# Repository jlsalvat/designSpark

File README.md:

# designSpark V10 files
cartes et bibliothèques

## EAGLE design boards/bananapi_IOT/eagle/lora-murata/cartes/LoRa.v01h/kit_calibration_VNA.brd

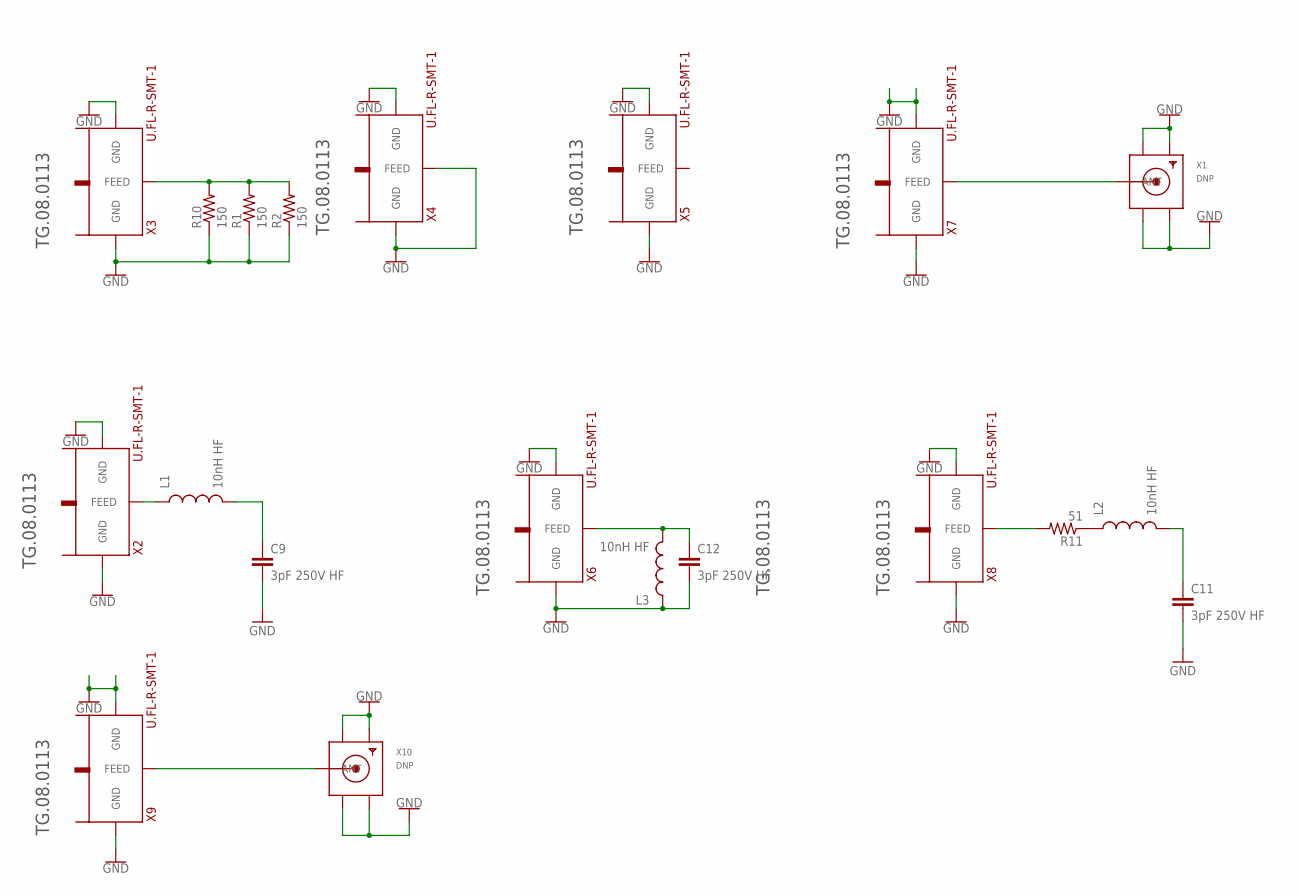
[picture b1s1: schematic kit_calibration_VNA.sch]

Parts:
C9, C11, C12: 3pF 250V HF; 0603-CAP
L1, L2, L3: 10nH HF; 0603
R1, R2, R10: 150; 0603-RES
R11: 51; 0603-RES
X1, X10: DNP; SMA_EDGELAUNCH; DIGIKEY CON-SMA-EDGE-S-ND
X2, X3, X4, X5, X6, X7, X8, X9: U.FL-R-SMT-1

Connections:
GND: C9.2, C11.2, C12.2, L3.1, R1.1, R2.1, R10.1, X1.GND@1 (GND4), X1.GND@2 (GND3), X1.GND@3 (GND2), X1.GND@4 (GND1), X2.P$1 (GND), X2.P$2 (GND), X3.P$1 (GND), X3.P$2 (GND), X4.P$1 (GND), X4.P$2 (GND), X4.P$3 (FEED), X5.P$1 (GND), X5.P$2 (GND), X6.P$1 (GND), X6.P$2 (GND), X7.P$1 (GND), X7.P$2 (GND), X8.P$1 (GND), X8.P$2 (GND), X9.P$1 (GND), X9.P$2 (GND), X10.GND@1 (GND4), X10.GND@2 (GND3), X10.GND@3 (GND2), X10.GND@4 (GND1)
unnamed: X9.P$3 (FEED), X10.P (ANT)
unnamed: C9.1, L1.2
unnamed: L2.1, R11.1
unnamed: R1.2, R2.2, R10.2, X3.P$3 (FEED)
unnamed: L1.1, X2.P$3 (FEED)
unnamed: R11.2, X8.P$3 (FEED)
unnamed: C11.1, L2.2
unnamed: C12.1, L3.2, X6.P$3 (FEED)
unnamed: X1.P (ANT), X7.P$3 (FEED)

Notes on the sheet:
TG.08.0113

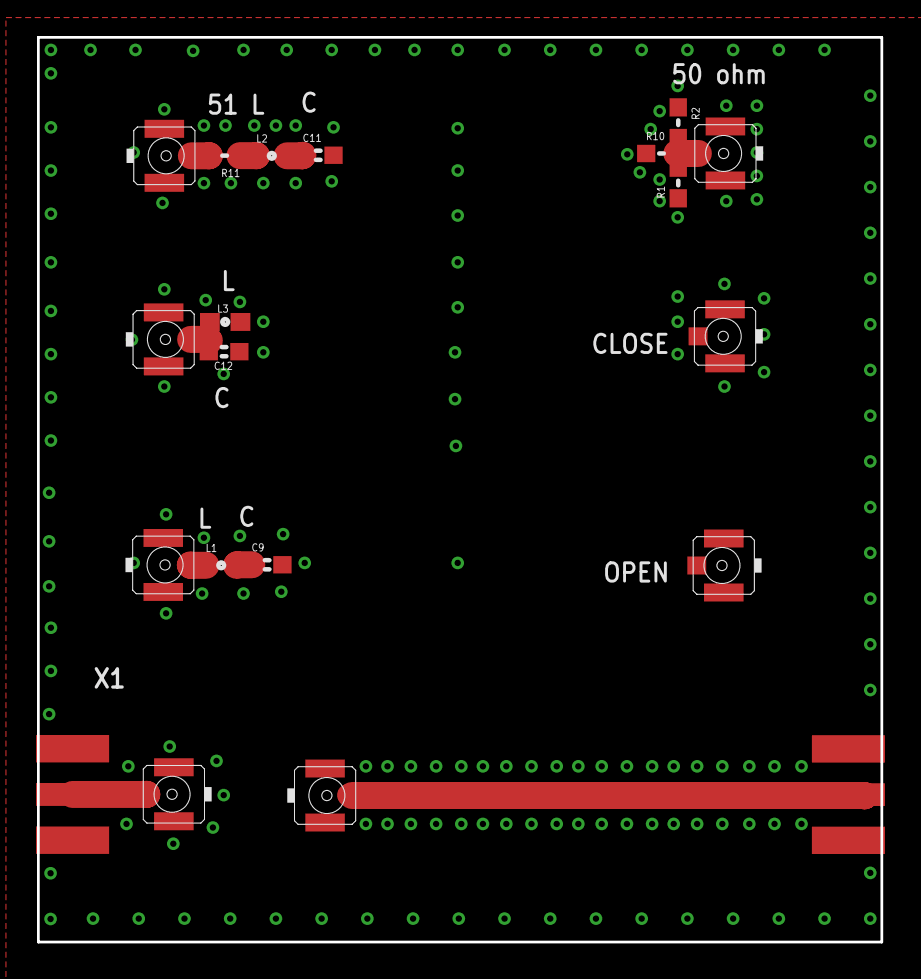
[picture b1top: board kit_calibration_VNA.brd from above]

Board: 2 copper layers, 46.9 x 50.3 mm, 20 parts (0 on the bottom side), 10 nets.

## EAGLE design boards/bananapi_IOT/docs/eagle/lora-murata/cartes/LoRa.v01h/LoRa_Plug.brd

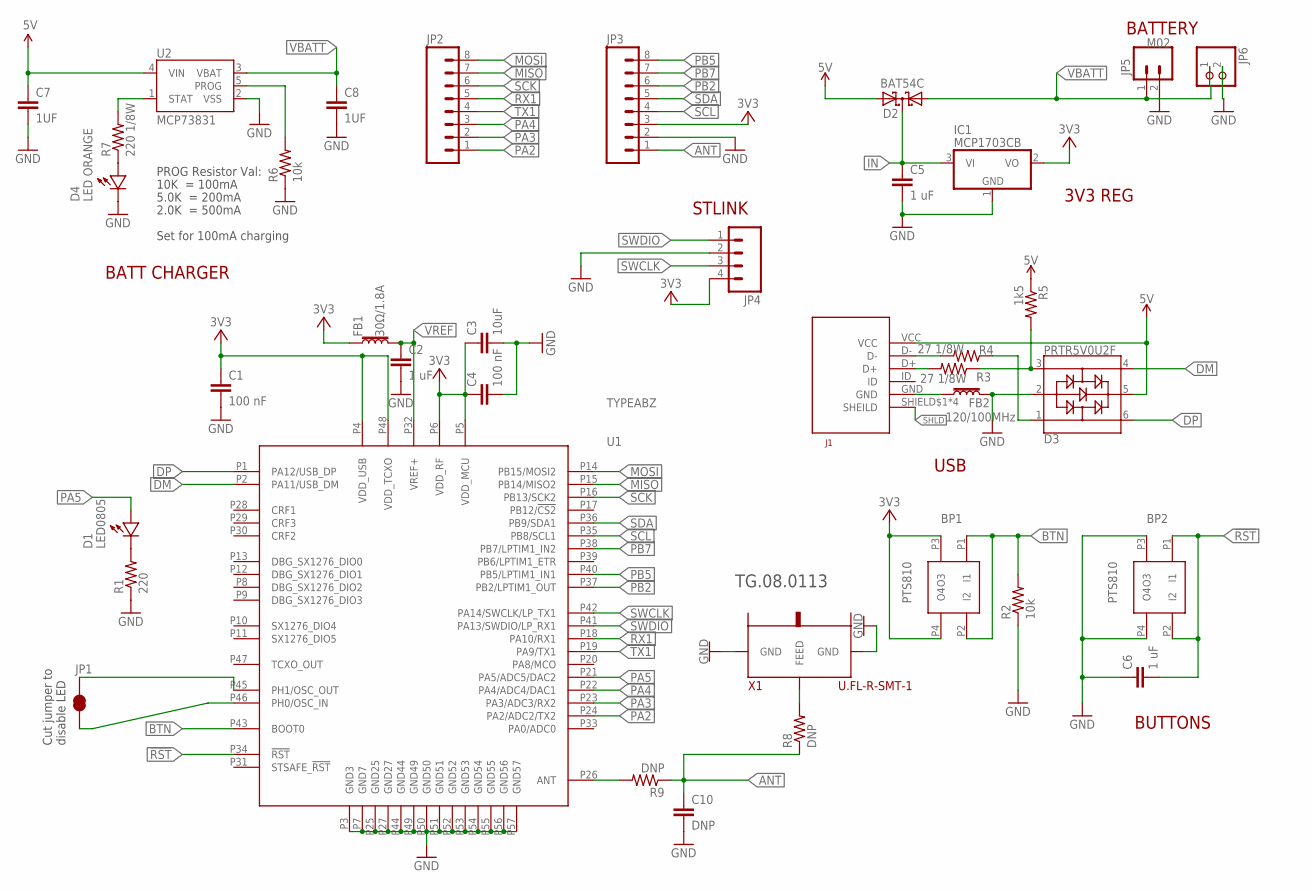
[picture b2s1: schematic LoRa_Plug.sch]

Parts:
BP1, BP2: PTS810; C&KTACTILESWITCH
C1, C4: 100 nF; 0603-CAP
C2, C5, C6: 1 uF; 0603-CAP
C3: 10uF; 0603-CAP
C7, C8: 1UF; 0603-CAP
C10: DNP; 0603-CAP
D1: LED0805; 0805-LED
D2: BAT54C; SOT23
D3: PRTR5V0U2F; SOT886; DIGIKEY 1727-4161-1-ND
D4: LED ORANGE; 0805-LED; DIGIKEY 160-1413-2-ND
FB1: 30Ω/1.8A; 0603; DIGIKEY BLM18EG331TN1D
FB2: 120/100MHz; 0603; DIGIKEY BLM18EG331TN1D
IC1: MCP1703CB; SOT23
J1: 10118193-0001LF
JP1: JUMPER-SMT_2_NC_TRACE_SILK; SMT-JUMPER_2_NC_TRACE_SILK
JP2, JP3: M08; 1X08
JP4: M04PTH; 1X04
JP5: M02; 1X02
JP6: JST_2PIN-THM; JST-PH-2-THM
R1: 220; 0603-RES
R2, R6: 10k; 0603-RES
R3, R4: 27 1/8W; 0603-RES
R5: 1k5; 0603-RES
R7: 220 1/8W; 0805; DIGIKEY A129741TR-ND
R8, R9: DNP; 0603-RES
U1: TYPEABZ
U2: MCP73831; SOT23-5:1; DIGIKEY MCP73831T-2DCI/OTCT-ND
X1: U.FL-R-SMT-1

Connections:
3V3: BP1.P3 (O3), BP1.P4 (O4), C1.1, C3.1, C4.1, FB1.1, IC1.2 (VO), JP3.3, JP4.4, U1.P4 (VDD_USB), U1.P5 (VDD_MCU), U1.P6 (VDD_RF), U1.P48 (VDD_TCXO)
5V: C7.1, D2.2 (A2), D3.5, J1.VCC, R5.1, U2.4 (VIN)
!RST: BP2.P1 (I1), BP2.P2 (I2), C6.2, U1.P34 (!RST)
ANT: C10.1, JP3.1, R8.1, R9.1
BTN: BP1.P1 (I1), BP1.P2 (I2), R2.2, U1.P43 (BOOT0)
DM: D3.4, U1.P2 (PA11/USB_DM)
DP: D3.6, U1.P1 (PA12/USB_DP)
GND: BP2.P3 (O3), BP2.P4 (O4), C1.2, C2.2, C3.2, C4.2, C5.2, C6.1, C7.2, C8.2, C10.2, D3.2, D4.MINUS, FB2.2, IC1.1 (GND), JP3.2, JP4.2, JP5.2, JP6.2 (1), R1.1, R2.1, R6.1, U1.P3 (GND3), U1.P7 (GND7), U1.P25 (GND25), U1.P27 (GND27), U1.P44 (GND44), U1.P49 (GND49), U1.P50 (GND50), U1.P51 (GND51), U1.P52 (GND52), U1.P53 (GND53), U1.P54 (GND54), U1.P55 (GND55), U1.P56 (GND56), U1.P57 (GND57), U2.2 (VSS), X1.P$1 (GND), X1.P$2 (GND)
IN: C5.1, D2.3 (CC), IC1.3 (VI)
MISO: JP2.7, U1.P15 (PB14/MISO2)
MOSI: JP2.8, U1.P14 (PB15/MOSI2)
unnamed: D1.MINUS, R1.2
unnamed: R9.2, U1.P26 (ANT)
unnamed: JP1.2, U1.P45 (PH1/OSC_OUT)
unnamed: J1.D-, R4.2
unnamed: J1.D+, R3.2
unnamed: FB2.1, J1.GND
unnamed: JP1.1, U1.P46 (PH0/OSC_IN)
unnamed: D4.PLUS, R7.1
unnamed: R8.2, X1.P$3 (FEED)
PA2: JP2.1, U1.P24 (PA2/ADC2/TX2)
PA3: JP2.2, U1.P23 (PA3/ADC3/RX2)
PA4: JP2.3, U1.P22 (PA4/ADC4/DAC1)
PA5: D1.PLUS, U1.P21 (PA5/ADC5/DAC2)
PB2: JP3.6, U1.P37 (PB2/LPTIM1_OUT)
PB5: JP3.8, U1.P40 (PB5/LPTIM1_IN1)
PB7: JP3.7, U1.P38 (PB7/LPTIM1_IN2)
PROG1: R6.2, U2.5 (PROG)
RX1: JP2.5, U1.P18 (PA10/RX1)
SCK: JP2.6, U1.P16 (PB13/SCK2)
SCL: JP3.4, U1.P35 (PB8/SCL1)
SDA: JP3.5, U1.P36 (PB9/SDA1)
SHLD: J1.SHIELD$1 (SHEILD), J1.SHIELD$2 (SHEILD), J1.SHIELD$3 (SHEILD), J1.SHIELD$4 (SHEILD)
STAT1: R7.2, U2.1 (STAT)
SWCLK: JP4.3, U1.P42 (PA14/SWCLK/LP_TX1)
SWDIO: JP4.1, U1.P41 (PA13/SWDIO/LP_RX1)
TX1: JP2.4, U1.P19 (PA9/TX1)
USB_D+: D3.3, R3.1, R5.2
USB_D-: D3.1, R4.1
VBATT: C8.1, D2.1 (A1), JP5.1, JP6.1 (2), U2.3 (VBAT)
VREF: C2.1, FB1.2, U1.P32 (VREF+)

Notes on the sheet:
Cut jumper to disable LED
Set for 100mA charging
10K = 100mA
5.0K = 200mA
2.0K = 500mA
PROG Resistor Val:
BATT CHARGER
3V3 REG
BATTERY
STLINK
USB
BUTTONS
TG.08.0113

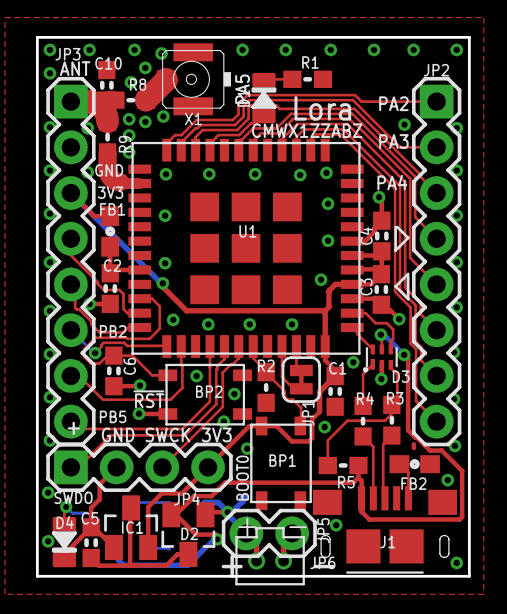
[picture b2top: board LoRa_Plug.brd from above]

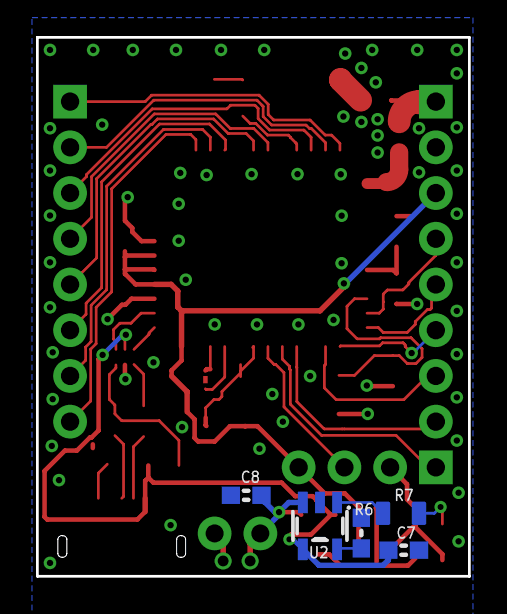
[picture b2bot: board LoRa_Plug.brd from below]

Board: 2 copper layers, 24.0 x 29.9 mm, 37 parts (5 on the bottom side), 41 nets.

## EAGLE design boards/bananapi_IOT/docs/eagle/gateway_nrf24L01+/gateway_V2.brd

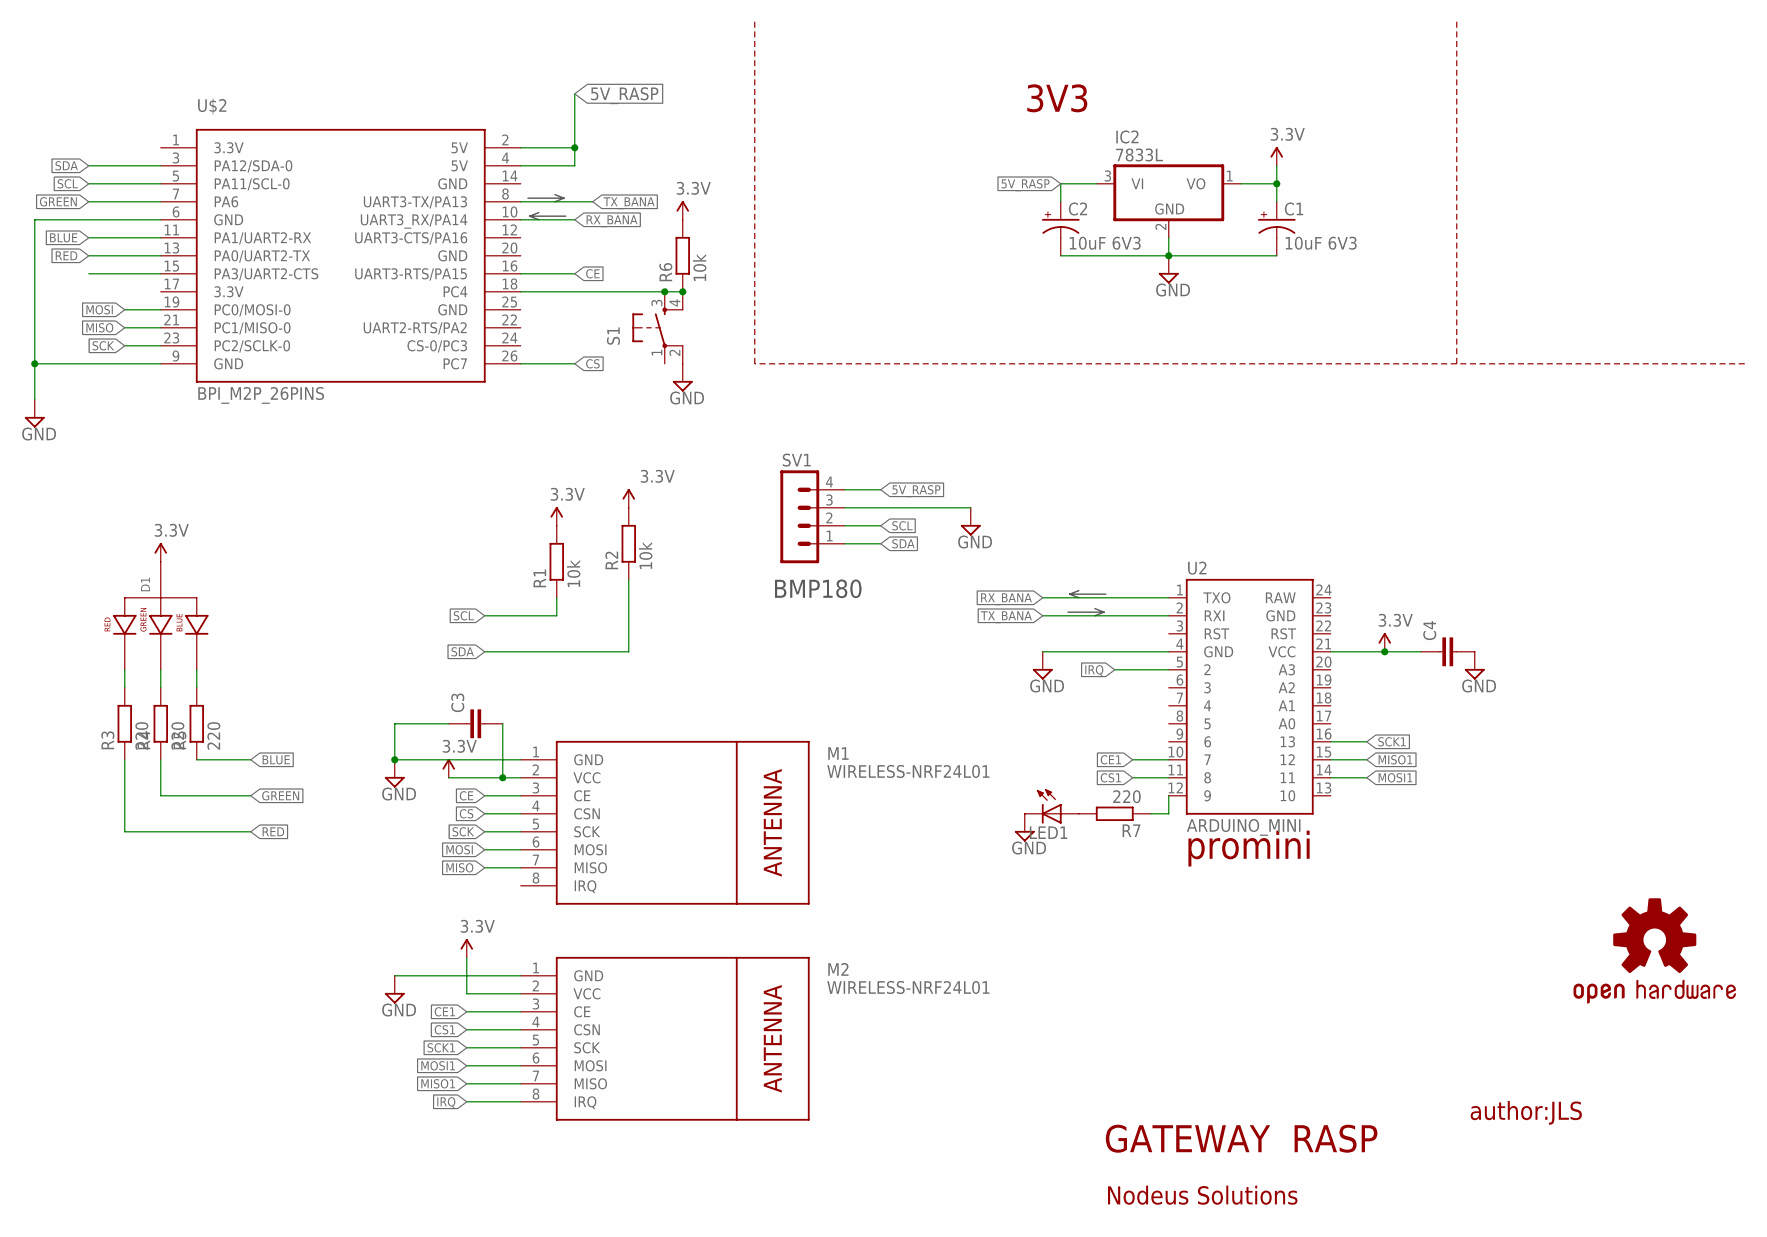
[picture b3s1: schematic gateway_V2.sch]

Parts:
C1, C2: 10uF 6V3; CPOL-RADIAL-100UF-25V
C3, C4: C050-035X075
D1: LED-RGB-CA-THRUCLEAR; LED-RGB-THRU
IC2: 7833L; TO92L
LED1: LED3MM
LOGO1: OSHW-LOGOMINI; OSHW-LOGO-MINI
M1, M2: WIRELESS-NRF24L01
R1, R2, R6: 10k; 0207/10
R3, R4, R5, R7: 220; 0207/10
S1: PUSH_BUTTONPTH; TACTILE-PTH
SV1: CON_HE14-4P; MA04-1
U2: ARDUINO_MINI
U$2: BPI_M2P_26PINS; 13X2-PTH

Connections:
3.3V: U$2.1 (3.3V), U$2.17 (3.3V)
5V_RASP: C2.1 (+), IC2.3 (VI), SV1.4, U$2.2 (5V), U$2.4 (5V)
BLUE: R5.1, U$2.11 (PA1/UART2-RX)
CE: M1.3 (CE), U$2.16 (UART3-RTS/PA15)
CE1: M2.3 (CE), U2.10 (7)
CS: M1.4 (CSN), U$2.26 (PC7)
CS1: M2.4 (CSN), U2.11 (8)
GND: C1.2 (-), C2.2 (-), C3.1, C4.2, IC2.2 (GND), LED1.K (C), M1.1 (GND), M2.1 (GND), S1.2, SV1.3, U2.4 (GND), U$2.6 (GND), U$2.9 (GND), U$2.20 (GND), U$2.25 (GND)
GREEN: R4.1, U$2.7 (PA6)
IRQ: M2.8 (IRQ), U2.5 (2)
MISO: M1.7 (MISO), U$2.21 (PC1/MISO-0)
MISO1: M2.7 (MISO), U2.15 (12)
MOSI: M1.6 (MOSI), U$2.19 (PC0/MOSI-0)
MOSI1: M2.6 (MOSI), U2.14 (11)
unnamed: R6.1, S1.3, S1.4, U$2.18 (PC4)
unnamed: R7.1, U2.12 (9)
unnamed: LED1.A, R7.2
unnamed: D1.1 (RED_CATHODE), R3.2
unnamed: D1.3 (GREEN_CATHODE), R4.2
unnamed: D1.4 (BLUE_CATHODE), R5.2
RED: R3.1, U$2.13 (PA0/UART2-TX)
RX_BANA: U2.1 (TXO), U$2.10 (UART3_RX/PA14)
SCK: M1.5 (SCK), U$2.23 (PC2/SCLK-0)
SCK1: M2.5 (SCK), U2.16 (13)
SCL: R1.1, SV1.2, U$2.5 (PA11/SCL-0)
SDA: R2.1, SV1.1, U$2.3 (PA12/SDA-0)
TX_BANA: U2.2 (RXI), U$2.8 (UART3-TX/PA13)
VCC: C1.1 (+), C3.2, C4.1, D1.2 (ANODE), IC2.1 (VO), M1.2 (VCC), M2.2 (VCC), R1.2, R2.2, R6.2, U2.21 (VCC)

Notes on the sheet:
GATEWAY RASP
author:JLS
Nodeus Solutions
promini
3V3
BMP180

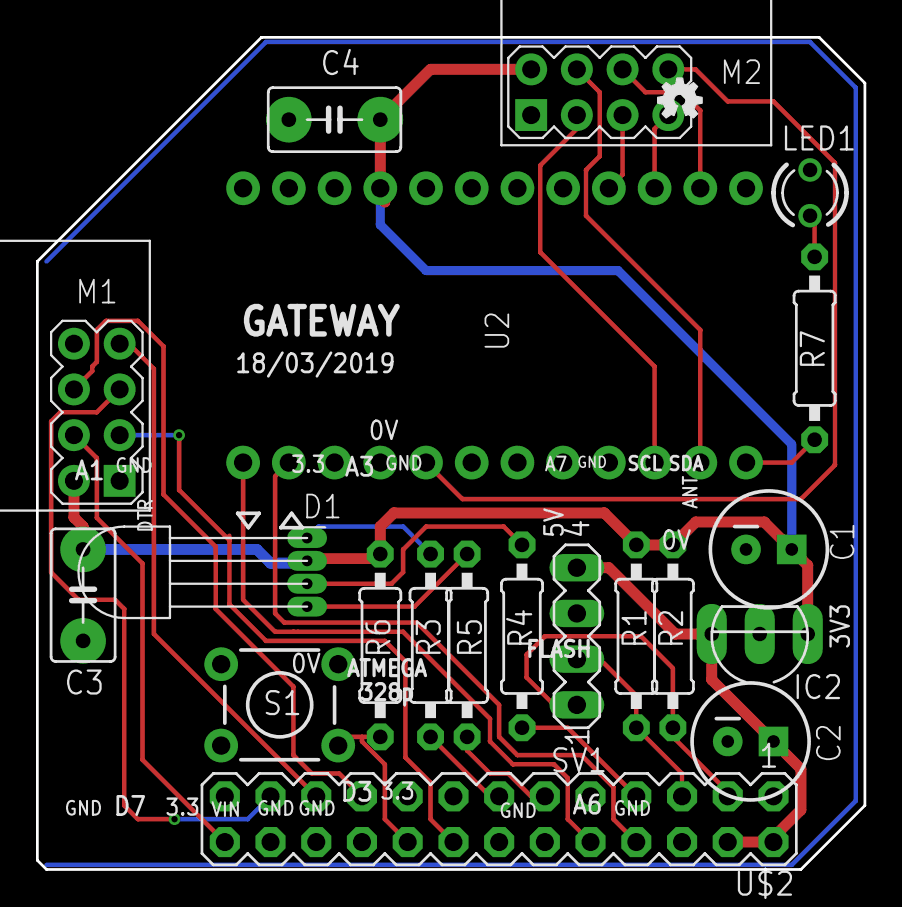
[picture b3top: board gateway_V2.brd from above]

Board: 2 copper layers, 46.0 x 46.2 mm, 22 parts (0 on the bottom side), 28 nets.

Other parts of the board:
DRILEGEND: DRILEGEND

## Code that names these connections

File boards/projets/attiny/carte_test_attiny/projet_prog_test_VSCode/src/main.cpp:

#include <Arduino.h>
#include "SoftwareSerial.h"
#include "rgb_lcd.h"

#ifndef cbi
#define cbi(sfr, bit) (_SFR_BYTE(sfr) &= ~_BV(bit))
#endif
#ifndef sbi
#define sbi(sfr, bit) (_SFR_BYTE(sfr) |= _BV(bit))
#endif
// ATMEL ATTINY84 / ARDUINO
//
//                                 +-\/-+
//                            VCC  1|    |14  GND
//                   (D  0)  PB0  2|    |13  AREF (D 10)  TX
//                  (D  1)  PB1  3|    |12  PA1  (D  9)  LED1
//                          PB3  4|    |11  PA2  (D  8)  RX
//  PWM  BP INT0   (D  2)  PB2  5|    |10  PA3  (D  7) LED2
//  PWM  POT       (D  3)  PA7  6|    |9   PA4  (D  6) SCK
//  PWM  MOSI      (D  4)  PA6  7|    |8   PA5  (D  5) MISO       PWM
//                               +----+
const int LED1 = 9;
const int LED2 = 7;
const int BP = 2;
const int TX = 10;
const int RX = 8;
const int POT = 3;

int valeur_potentiometre;

SoftwareSerial mySerial(RX, TX); // RX, TX

rgb_lcd lcd;

//pb par défaut on utilise PA0 pour AREF pour l'ADC de l'attiny.
// donc analogRead() ne fonctionne pas car AREF=0, ca renvoie 0
//changer la carte et mettre PA0=Vcc

void analog_voie(int n){
  //0x07 (0x27) REFS1 REFS0 MUX5 MUX4 MUX3 MUX2 MUX1 MUX0 ADMUX
  //REFS1 REFS0 Voltage Reference Selection
  //0     0     VCC used as analog reference, disconnected from PA0 (AREF).
   ADMUX=n&0x7;// on choisie PA0,PA1,PA2,... et Vcc
}
int analog_conversion(){
    sbi(ADCSRA, ADSC); //Start conversion
  while(ADCSRA & (1<<ADSC)); //Wait for conversion to complete.
  uint8_t low = ADCL;
  uint8_t high = ADCH;
  return (high << 8) | low;
}

void setup()
{
  // Open serial communications and wait for port to open:
  mySerial.begin(4800);
  /*  while (!Serial) {
      ; // wait for serial port to connect. Needed for native USB port only
    }*/

  mySerial.println("Hello, world?");
  // put your setup code here, to run once:
  pinMode(LED1, OUTPUT);
  pinMode(LED2, OUTPUT);
  pinMode(BP, INPUT_PULLUP);
  analog_voie(7);//on choisit PA7
    lcd.begin(16, 2);
    // Print a message to the LCD.
    lcd.print("hello, world!");
    delay(1000);
}


void loop()
{
    // scroll 13 positions (string length) to the left

  // put your main code here, to run repeatedly:
 // valeur_potentiometre= analogRead(POT);//marche pas
  valeur_potentiometre=analog_conversion();
  mySerial.println(valeur_potentiometre);
  float tension=valeur_potentiometre*5.0/1024;
  lcd.clear();
  lcd.blinkLED();
  lcd.print("pot=");
  lcd.print(tension);
  lcd.print(" V");
  digitalWrite(LED1, !digitalRead(BP));
  digitalWrite(LED2, HIGH);
  delay(200);
  digitalWrite(LED1, !digitalRead(BP));
  digitalWrite(LED2, LOW);
  delay(200);
}

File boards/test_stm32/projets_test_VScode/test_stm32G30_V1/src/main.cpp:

#include <Arduino.h>
#include "rgb_lcd.h"

HardwareSerial DebugSerial(PB7, PB6); // compiles, can also use (USART1)

const int LED1 = PA11;
const int LED2 = PC6;
const int BP = 2;
const int BP1 = PA0;
const int BP2 = PA1;
const int POT = PA5;

int valeur_potentiometre;
rgb_lcd lcd;

void setup()
{
  // put your setup code here, to run once:
  pinMode(LED1, OUTPUT);
  pinMode(LED2, OUTPUT);
  Serial.begin(9600);
  pinMode(BP1, INPUT_PULLUP);
  pinMode(BP2, INPUT_PULLUP);
  DebugSerial.begin(9600);
    lcd.begin(16, 2);
    // Print a message to the LCD.
    lcd.print("hello, world!");
    delay(1000);
}

void loop()
{
   static int cpt = 0;
    // put your main code here, to run repeatedly:
   digitalToggle(LED1);
    digitalToggle(LED2);
    delay(200);
    Serial.print("serial:");
    Serial.println(cpt);

    cpt++;
    valeur_potentiometre = analogRead(POT);
    int tension=valeur_potentiometre*32;

  lcd.clear();
  lcd.blinkLED();
  lcd.setCursor(0,0);
  lcd.print("pot=");
  lcd.print(tension/10000);
  lcd.print(".");
  lcd.print(tension%10000);
  lcd.print(" V");
  lcd.setCursor(0,1);
      lcd.print("BP1=");
      lcd.print(digitalRead(BP1));
      lcd.print("  BP2=");
      lcd.print(digitalRead(BP2));
    Serial.print("cpt=");
    Serial.println(cpt);
      DebugSerial.print("Debug:");
      DebugSerial.print(digitalRead(BP1));
      DebugSerial.print(" ");
      DebugSerial.print(digitalRead(BP2));
      DebugSerial.print(" ");
    DebugSerial.println(valeur_potentiometre);
}

/*
void poubelle(){

    lcd.clear();
  lcd.blinkLED();
  lcd.print("pot=");
  lcd.print(valeur_potentiometre);
 // valeur_potentiometre = analogRead(POT);
  DebugSerial.println(valeur_potentiometre);
  int tension = valeur_potentiometre * 3300 / 4096;
  lcd.clear();
  lcd.blinkLED();
  lcd.print("pot=");
  lcd.print(tension/100);
  lcd.print(".");
  lcd.print(tension%100);
  Serial.println(tension);
  lcd.print(" V");
  digitalWrite(LED1, !digitalRead(BP1));
  digitalWrite(LED2, !digitalRead(BP1));
  delay(100);
}*/

/*#include "Wire.h"
 
void setup(){
    Wire.begin();    
    Serial.begin(9600);
} 
 
void loop(){
    byte error, address;
    int nDevices;
 
    Serial.println("Scanning...");
 
    nDevices = 0;
    for(address = 8; address < 127; address++ ){
        Wire.beginTransmission(address);
        error = Wire.endTransmission();
 
        if (error == 0){
            Serial.print("I2C device found at address 0x");
            if (address < 16)
                Serial.print("0");
            Serial.print(address,HEX);
            Serial.println(" !");
 
            nDevices++;
        }
        else if (error == 4) {
            Serial.print("Unknow error at address 0x");
            if (address < 16)
                Serial.print("0");
            Serial.println(address,HEX);
        } 
    }
    if (nDevices == 0)
        Serial.println("No I2C devices found\n");
    else
        Serial.println("done\n");
 
    delay(5000);
}*/

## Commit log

2022-01-08 cartes auto1 BUT GEII
    Premier commit des cartes auto1 BUT GEII
2022-01-08 SAE Flipper BUT GEII
    Premier commit des cartes SAE Flipper BUT GEII
2022-01-08 ajout bibliothèques DSPCB V10 et réorganisation des dossiers
2022-01-08 ajout projet poule et réorganisation des fichiers
2022-01-08 modif readme
2022-01-10 version jlcpcb
    version envoyée à JLSPCB
2022-01-20 Create proj_etud_BUT2 (rsbom).xlsx
    add xls bom list
2022-01-22 ajout images maquette moteur
2022-01-24 ajout lien 3D et réorganisation fichiers + fab 3D
2022-01-27 add M340 boards
2022-04-01 add librairies
    modbus initial a été modifié
2022-07-06 NEW
    nouvelle carte SAE ROBOT avec capteur de vitesse et opto-coupleurs
2022-07-06 ajout PCB pdf
2022-07-06 Mise à jour (Merci Christophe)
2022-10-06 modif carte commande
    ajout septembre modif carte commande, modif des valeurs de résistances et taille des connecteurs moteur
2022-10-07 ajouts pour SAE
2022-10-18 add carte pneumatique
    Carte pour TP pneumatique
2022-10-21 update Aline
2022-10-24 modif fichier excel
2023-04-12 ajout carte tiny
    Première carte uc tiny
2023-04-12 mise à jour
2023-04-14 ajout STM32 et mis à jour librairy
2023-05-02 update carte tiny (probleme placement condo)
2023-05-02 update STM32 8 pins
2023-05-10 update cartes et code
2023-05-23 upadte lorawan
    modif carte lorawan
2023-05-30 update rc5 tiny
2023-05-31 update code
2023-05-31 update all
2023-05-31 update prog tiny
2023-05-31 update pour 4P38
2023-06-08 update attiny
2023-06-08 update prog attiny
2023-09-22 update carte projet cms
2023-09-25 update board SAE four
    ajout grove
2023-09-27 update output et input M340
    mise à jour de output m340 qui est bugué et de input M340 ,déplacement douille, enlève les points tests, modif empreinte pins automates +-1mm, modif silscreen
2023-10-12 updates cartes et modif gerber
    modif sur carte de l'empreinte 20 broches automate (écartement de 0,5mm) et déplacement des douilles pour qu'elles soient identiques et ok pour le brasage.
2023-10-16 update carte étudiant F303 et cartes dégradées pour fab JLCPCB
2023-10-23 update F303
2023-10-29 update carte CAN
2023-10-29 modif update nom
2023-11-09 update christophe
    carte finale envoyé par Christophe JLCPCB
2023-12-20 add sae son
2024-02-16 update Michel
    mise à jour globale (fab du 15/02/24 JLCPCB)
2024-11-29 ajout super3 modbus
2025-02-19 update nrf24L01P_module_PCB on my_lib_tiny
2025-03-07 first update bananpi
2025-05-07 update schematic carte moteur

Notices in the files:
parts and their libraries:
SparkFun-Aesthetics: Licensing: Creative Commons ShareAlike 4.0 International - https://creativecommons.org/licenses/by-sa/4.0
